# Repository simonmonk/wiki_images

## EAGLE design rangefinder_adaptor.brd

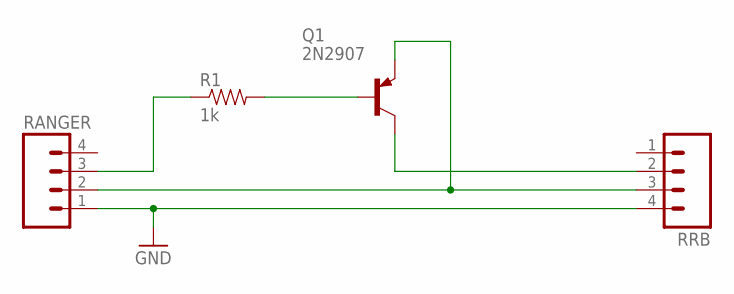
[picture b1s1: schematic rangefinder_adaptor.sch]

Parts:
Q1: 2N2907; TO92-EBC-OVAL
R1: 1k; AXIAL-0.4
RANGER: M04LONGPADS; 1X04_LONGPADS
RRB: M04LONGPADS; 1X04_LONGPADS

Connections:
GND: RANGER.1, RRB.4
unnamed: Q1.E, RANGER.2, RRB.3
unnamed: R1.P$1 (1), RANGER.3
unnamed: Q1.B, R1.P$2 (2)
unnamed: Q1.C, RRB.2

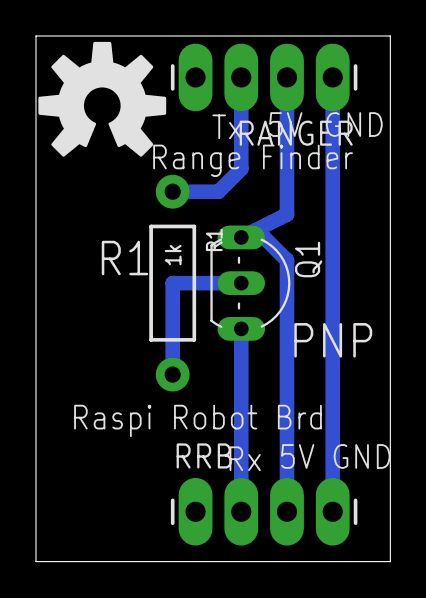
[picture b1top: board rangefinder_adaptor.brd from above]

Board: 2 copper layers, 19.7 x 29.2 mm, 5 parts (0 on the bottom side), 5 nets.

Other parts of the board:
U$1: OSHW-LOGO-L

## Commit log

2013-02-15 images
2013-02-19 stuff
2013-04-08 added image
2013-06-01 3-15
2014-01-31 added one
2014-03-21 rrb2
